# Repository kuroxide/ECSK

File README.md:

# ECSK
An Extra/Exceptionally/Extremely/Ehhhhhhh Cheap Steno Keyboard based on a Raspberry Pi Pico

## Rationale
The ECSK designed to be simple and cheap enough that one person could plausibly build it themselves using tools and services that are readily available to them.
- The case can be easily 3D printed, or ignored entirely if using PCB-mount switches.
- The controller (Raspberry Pi Pico) is cheap and easy to source. It is also simple to program provided you have a basic understanding of Python and can read instructions. (However, the controller also turns out to be a potential caveat.)
- Through-hole components are easier to solder.
- The PCB can be ordered from any of several fabrication services. It can also be home-made if you have the setup for it (although this is out of the scope of the project.)
- If really necessary, the PCB could theoretically be replaced with a piece of plastic with some holes in the right places (this is also outside the scope of the project)

## Caveats
- The aforementioned controller. N-key rollover (which is essentially essential for a stenography keyboard) is somewhat patchy on KMK firmware. It is, as far as I know, not officially implemented but still somehow works half the time.
- Ergonomics. The layout has the hands very close together which can be uncomfortable. A wrist rest is recommended for long periods of use. (You can freely edit the design though.)
- Keycaps. F10 profile keycaps are recommended, but they can be difficult to get a hold of. G20 is also recommended. XDA profile keycaps are easier to get, but are less ideal for stenography.
- Repairability. This only applies if you use the case. In order to swap out a switch with the case, every single switch has to be desoldered.
- Speaking of soldering, you need a soldering iron.

## Parts
With that out of the way, we can get to the parts list.
- Raspberry Pi Pico ($15AUD).
- 24 MX-style switches (~$25AUD). Very light linears are recommended (remember, you will be pressing lots of keys at once.) Gateron clears are a goodd choice. Get PCB-mount switches if you can't make the case, or if you care about repairability.
- 24 diodes ($12-$30AUD). I used some very cheap 1N4002 diodes (200 for $12AUD). Basically any through-hole diodes with a DO-41 footprint or 7.62mm pin pitch will work.
- 24 keycaps ($20-$infinityAUD). This really just depends on how much you're willing to spend. I used some blank XDA profile caps which I got for $20AUD.
- The PCB. The price for this is difficult to pinpoint. I got mine produced by JLCPCB for about $40AUD shipped. Keep in mind most fabs have a minimum order quantity.
- **Note: the case will not work with v2 of the PCB!** The case. This is free if you have a) A 3D printer ready to go or b) A friend/school/acquaintance who will let you use their printer. Otherwise, you can order it to be made with some service. I suggest ditching the case entirely and just going with PCB-mount switches.

## Building the board
All components should be soldered to the top of the PCB (the face with the silkscreen markings.) \
Step 0. If you are using the case, print it out. Snap all the switches in place, LED slot facing the bottom edge of the PCB. The bottom is the long edge closest to the controller's footprint. \
Step 1. Solder in all the diodes. Bend the legs to a 7.62mm pitch, then put them through the holes in the PCB with the cathode (marked with a line) facing the bottom edge of the PCB. \
Step 2. Solder in the Pi Pico. Try to line up the USB port with the edge. One method is to use some pin headers to align it while you solder some of the pins, then remove the header and solder the rest. \
Step 3. Solder in the switches. This is pretty self-explanatory. If you are using the case, place the case upside-down and lower the PCB onto it with the bottom face facing outwards, aligning the switch pins. \
Step 4. Flash CircuitPython and KMK onto the Pi Pico. This can be done at anytime. If you are using the case, you can press the reset button through the small hole in the top. \
Step 5. Program the Pico (.uf2 file to be added to this repo soon™) \
Step 6. Check if it works. \
Step 7. Stenography time!

## Licensing
This is an open hardware project.

<br />This work is licensed under a <a rel="license" href="http://creativecommons.org/licenses/by-sa/4.0/">Creative Commons Attribution-ShareAlike 4.0 International License</a>.

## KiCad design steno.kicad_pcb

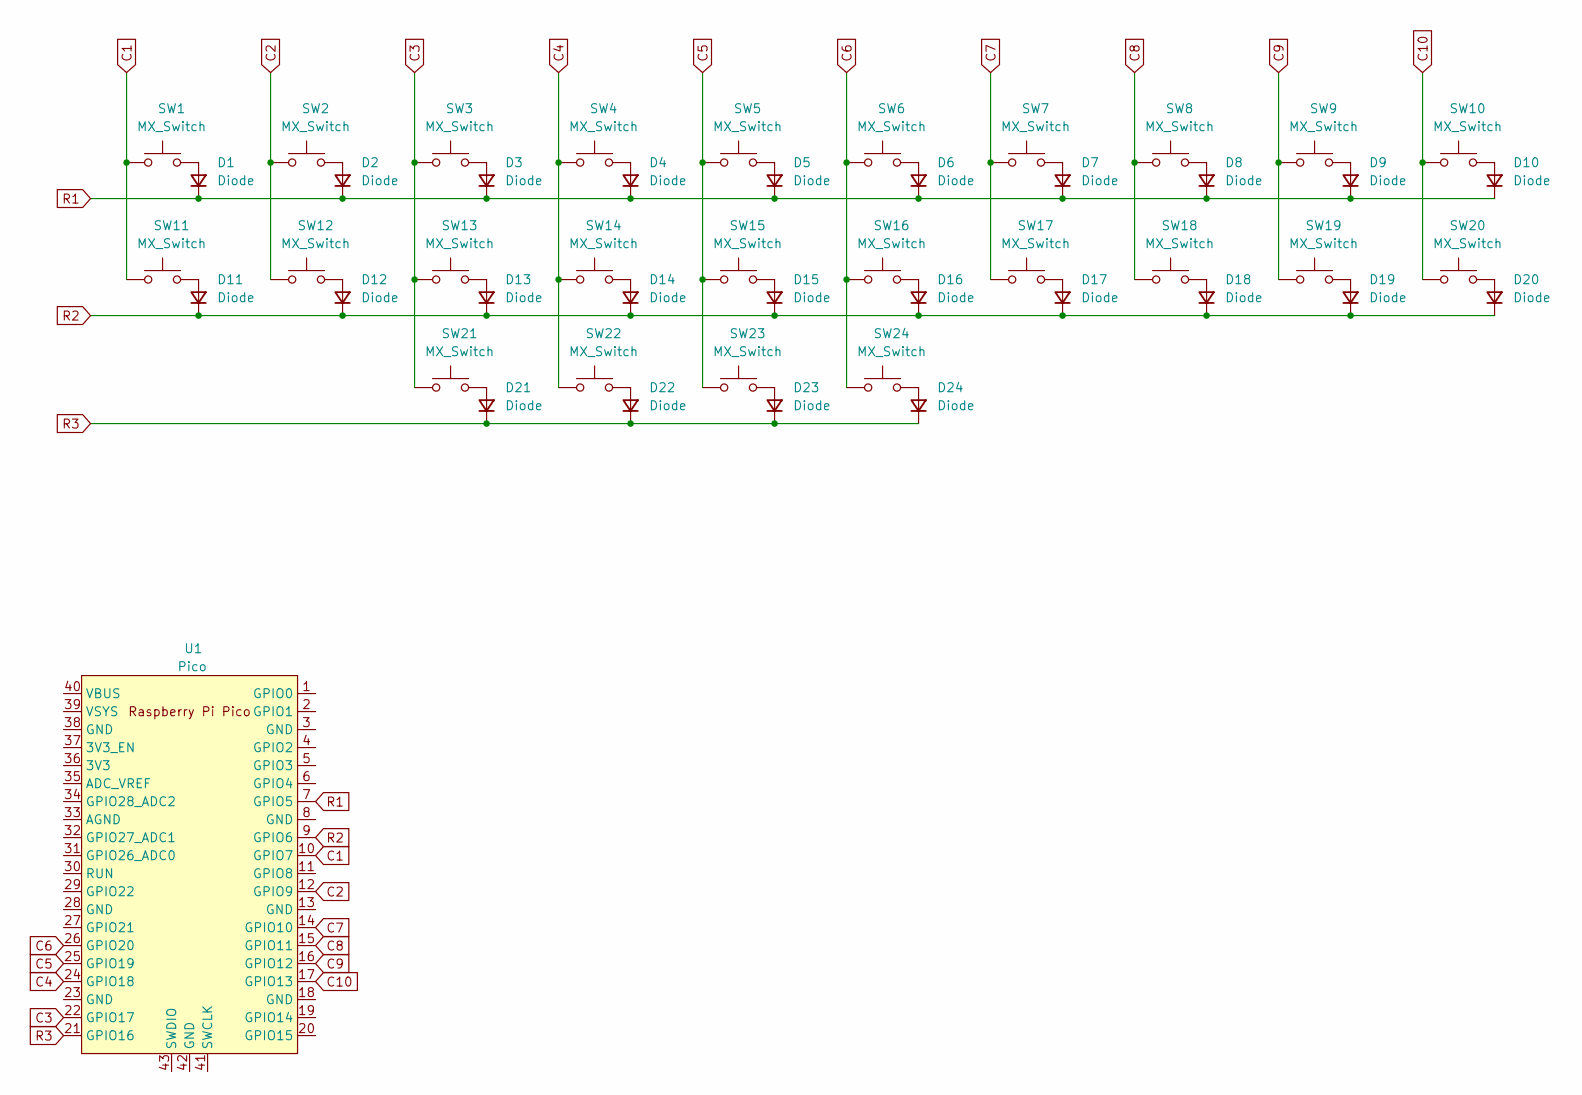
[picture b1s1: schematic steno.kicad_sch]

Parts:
D1, D2, D3, D4, D5, D6, D7, D8, D9, D10, D11, D12, D13, D14, D15, D16, D17, D18, D19, D20, D21, D22, D23, D24: Diode; D_DO-41_SOD81_P7.62mm_Horizontal
SW1, SW2, SW3, SW4, SW5, SW6, SW7, SW8, SW9, SW10, SW11, SW12, SW13, SW14, SW15, SW16, SW17, SW18, SW19, SW20, SW21, SW22, SW23, SW24: MX_Switch; SW_Cherry_MX_1.00u_PCB
U1: Pico; RPi_Pico_SMD_TH

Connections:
C1: SW1.1, SW11.1, U1.10 (GPIO7)
C2: SW2.1, SW12.1, U1.12 (GPIO9)
C3: SW3.1, SW13.1, SW21.1, U1.22 (GPIO17)
C4: SW4.1, SW14.1, SW22.1, U1.24 (GPIO18)
C5: SW5.1, SW15.1, SW23.1, U1.25 (GPIO19)
C6: SW6.1, SW16.1, SW24.1, U1.26 (GPIO20)
C7: SW7.1, SW17.1, U1.14 (GPIO10)
C8: SW8.1, SW18.1, U1.15 (GPIO11)
C9: SW9.1, SW19.1, U1.16 (GPIO12)
C10: SW10.1, SW20.1, U1.17 (GPIO13)
unnamed: D1.2 (A), SW1.2
unnamed: D2.2 (A), SW2.2
unnamed: D3.2 (A), SW3.2
unnamed: D4.2 (A), SW4.2
unnamed: D5.2 (A), SW5.2
unnamed: D6.2 (A), SW6.2
unnamed: D7.2 (A), SW7.2
unnamed: D8.2 (A), SW8.2
unnamed: D9.2 (A), SW9.2
unnamed: D10.2 (A), SW10.2
unnamed: D11.2 (A), SW11.2
unnamed: D12.2 (A), SW12.2
unnamed: D13.2 (A), SW13.2
unnamed: D14.2 (A), SW14.2
unnamed: D15.2 (A), SW15.2
unnamed: D16.2 (A), SW16.2
unnamed: D17.2 (A), SW17.2
unnamed: D18.2 (A), SW18.2
unnamed: D19.2 (A), SW19.2
unnamed: D20.2 (A), SW20.2
unnamed: D21.2 (A), SW21.2
unnamed: D22.2 (A), SW22.2
unnamed: D23.2 (A), SW23.2
unnamed: D24.2 (A), SW24.2
R1: D1.1 (K), D2.1 (K), D3.1 (K), D4.1 (K), D5.1 (K), D6.1 (K), D7.1 (K), D8.1 (K), D9.1 (K), D10.1 (K), U1.7 (GPIO5)
R2: D11.1 (K), D12.1 (K), D13.1 (K), D14.1 (K), D15.1 (K), D16.1 (K), D17.1 (K), D18.1 (K), D19.1 (K), D20.1 (K), U1.9 (GPIO6)
R3: D21.1 (K), D22.1 (K), D23.1 (K), D24.1 (K), U1.21 (GPIO16)

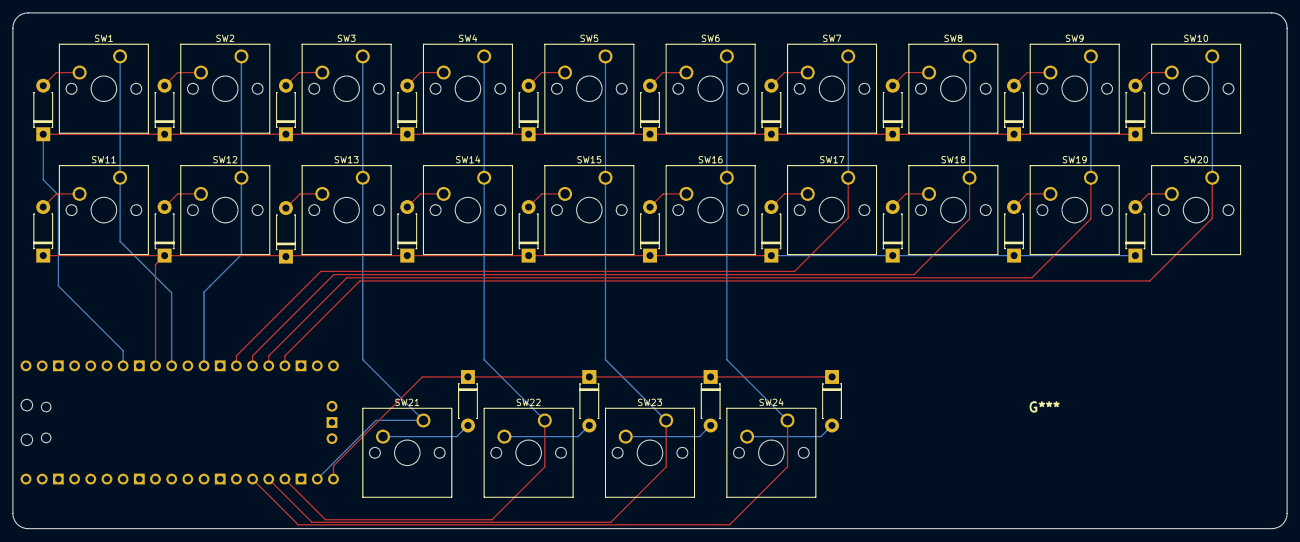
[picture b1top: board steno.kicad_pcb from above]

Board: 2 copper layers, 200.0 x 81.0 mm, 49 parts (1 on the bottom side), 37 nets.

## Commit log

2023-07-30 Add project files
2023-12-23 Update PCB schematics to ECSKv2 design
